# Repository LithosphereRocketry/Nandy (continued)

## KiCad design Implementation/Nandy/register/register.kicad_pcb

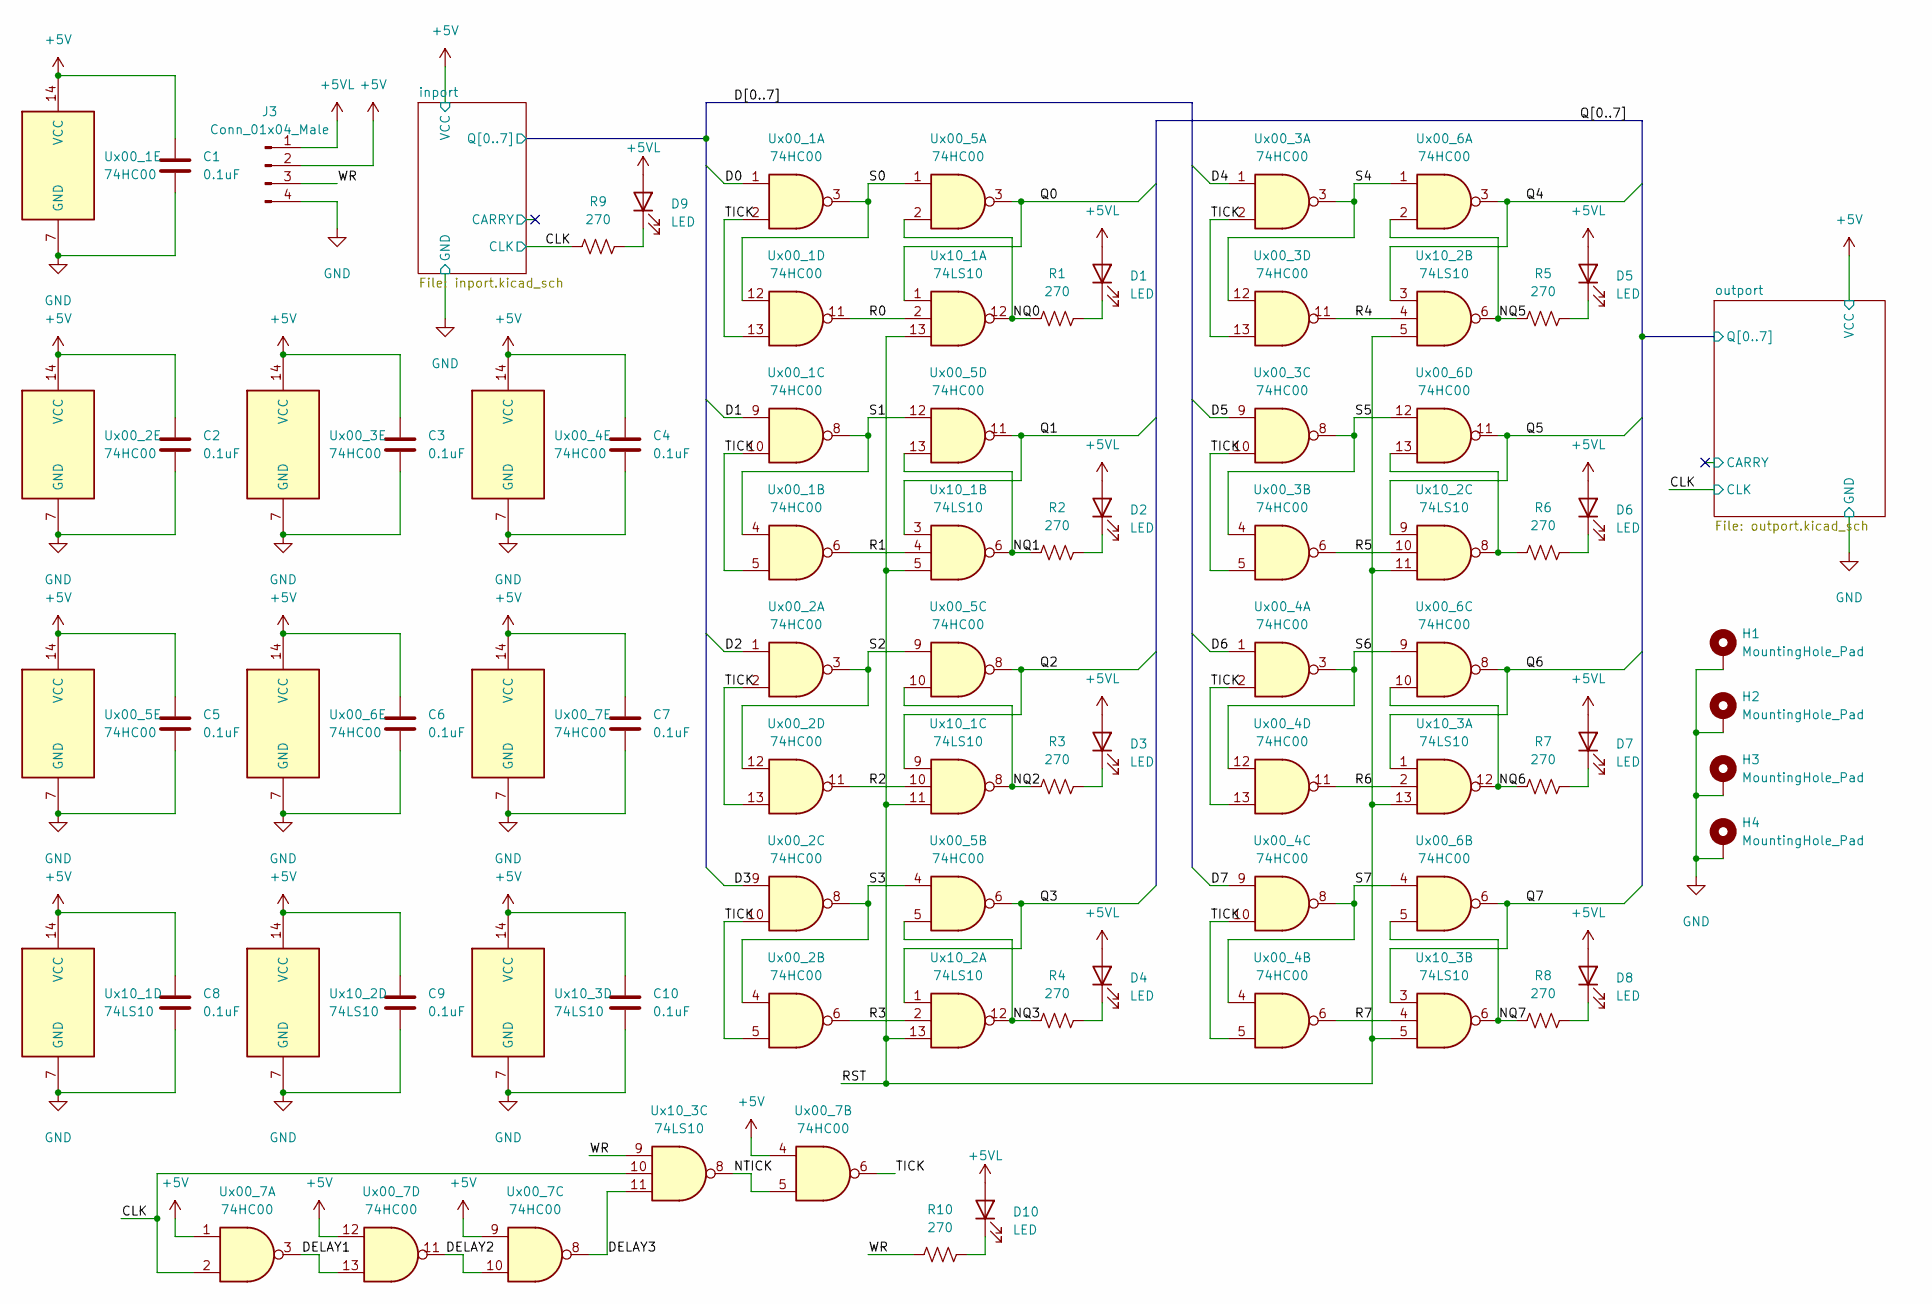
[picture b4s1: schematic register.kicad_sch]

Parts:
C1, C2, C3, C4, C5, C6, C7, C8, C9, C10: 0.1uF; C_Disc_D4.3mm_W1.9mm_P5.00mm
D1, D2, D3, D4, D5, D6, D7, D8, D9, D10: LED; LED_D5.0mm
H1, H2, H3, H4: MountingHole_Pad; MountingHole_3.2mm_M3_Pad_Via
J3: Conn_01x04_Male; SolderWire-0.5sqmm_1x04_P4.6mm_D0.9mm_OD2.1mm
R1, R2, R3, R4, R5, R6, R7, R8, R9, R10: 270; R_Axial_DIN0207_L6.3mm_D2.5mm_P7.62mm_Horizontal
Ux00_1, Ux00_2, Ux00_3, Ux00_4, Ux00_5, Ux00_6, Ux00_7: 74HC00; DIP-14_W7.62mm_Socket
Ux10_1, Ux10_2, Ux10_3: 74LS10; DIP-14_W7.62mm_Socket

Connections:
+5V: C1.1, C2.1, C3.1, C4.1, C5.1, C6.1, C7.1, C8.1, C9.1, C10.1, J3.2, Ux00_1.14 (VCC), Ux00_2.14 (VCC), Ux00_3.14 (VCC), Ux00_4.14 (VCC), Ux00_5.14 (VCC), Ux00_6.14 (VCC), Ux00_7.1, Ux00_7.4, Ux00_7.9, Ux00_7.12, Ux00_7.14 (VCC), Ux10_1.14 (VCC), Ux10_2.14 (VCC), Ux10_3.14 (VCC); also elsewhere on the board
+5VL: D1.2 (A), D2.2 (A), D3.2 (A), D4.2 (A), D5.2 (A), D6.2 (A), D7.2 (A), D8.2 (A), D9.2 (A), D10.2 (A), J3.1
/CLK: R9.1, Ux00_7.2, Ux10_3.10; also elsewhere on the board
/D0: Ux00_1.1; also elsewhere on the board
/D1: Ux00_1.9; also elsewhere on the board
/D2: Ux00_2.1; also elsewhere on the board
/D3: Ux00_2.9; also elsewhere on the board
/D4: Ux00_3.1; also elsewhere on the board
/D5: Ux00_3.9; also elsewhere on the board
/D6: Ux00_4.1; also elsewhere on the board
/D7: Ux00_4.9; also elsewhere on the board
/DELAY1: Ux00_7.3, Ux00_7.13
/DELAY2: Ux00_7.10, Ux00_7.11
/DELAY3: Ux00_7.8, Ux10_3.11
/NQ0: R1.1, Ux00_5.2, Ux10_1.12
/NQ1: R2.1, Ux00_5.13, Ux10_1.6
/NQ2: R3.1, Ux00_5.10, Ux10_1.8
/NQ3: R4.1, Ux00_5.5, Ux10_2.12
/NQ5: R5.1, Ux00_6.2, Ux10_2.6
/NQ6: R7.1, Ux00_6.10, Ux10_3.12
/NQ7: R8.1, Ux00_6.5, Ux10_3.6
/NTICK: Ux00_7.5, Ux10_3.8
/Q0: Ux00_5.3, Ux10_1.1; also elsewhere on the board
/Q1: Ux00_5.11, Ux10_1.3; also elsewhere on the board
/Q2: Ux00_5.8, Ux10_1.9; also elsewhere on the board
/Q3: Ux00_5.6, Ux10_2.1; also elsewhere on the board
/Q4: Ux00_6.3, Ux10_2.3; also elsewhere on the board
/Q5: Ux00_6.11, Ux10_2.9; also elsewhere on the board
/Q6: Ux00_6.8, Ux10_3.1; also elsewhere on the board
/Q7: Ux00_6.6, Ux10_3.3; also elsewhere on the board
/R0: Ux00_1.11, Ux10_1.2
/R1: Ux00_1.6, Ux10_1.4
/R2: Ux00_2.11, Ux10_1.10
/R3: Ux00_2.6, Ux10_2.2
/R4: Ux00_3.11, Ux10_2.4
/R5: Ux00_3.6, Ux10_2.10
/R6: Ux00_4.11, Ux10_3.2
/R7: Ux00_4.6, Ux10_3.4
/RST: Ux10_1.5, Ux10_1.11, Ux10_1.13, Ux10_2.5, Ux10_2.11, Ux10_2.13, Ux10_3.5, Ux10_3.13
/S0: Ux00_1.3, Ux00_1.12, Ux00_5.1
/S1: Ux00_1.4, Ux00_1.8, Ux00_5.12
/S2: Ux00_2.3, Ux00_2.12, Ux00_5.9
/S3: Ux00_2.4, Ux00_2.8, Ux00_5.4
/S4: Ux00_3.3, Ux00_3.12, Ux00_6.1
/S5: Ux00_3.4, Ux00_3.8, Ux00_6.12
/S6: Ux00_4.3, Ux00_4.12, Ux00_6.9
/S7: Ux00_4.4, Ux00_4.8, Ux00_6.4
/TICK: Ux00_1.2, Ux00_1.5, Ux00_1.10, Ux00_1.13, Ux00_2.2, Ux00_2.5, Ux00_2.10, Ux00_2.13, Ux00_3.2, Ux00_3.5, Ux00_3.10, Ux00_3.13, Ux00_4.2, Ux00_4.5, Ux00_4.10, Ux00_4.13, Ux00_7.6
/WR: J3.3, R10.1, Ux10_3.9
GND: C1.2, C2.2, C3.2, C4.2, C5.2, C6.2, C7.2, C8.2, C9.2, C10.2, H1.1, H2.1, H3.1, H4.1, J3.4, Ux00_1.7 (GND), Ux00_2.7 (GND), Ux00_3.7 (GND), Ux00_4.7 (GND), Ux00_5.7 (GND), Ux00_6.7 (GND), Ux00_7.7 (GND), Ux10_1.7 (GND), Ux10_2.7 (GND), Ux10_3.7 (GND); also elsewhere on the board
unnamed: D1.1 (K), R1.2
unnamed: D2.1 (K), R2.2
unnamed: D3.1 (K), R3.2
unnamed: D4.1 (K), R4.2
unnamed: D5.1 (K), R5.2
unnamed: D6.1 (K), R6.2
unnamed: D7.1 (K), R7.2
unnamed: D8.1 (K), R8.2
unnamed: D9.1 (K), R9.2
unnamed: D10.1 (K), R10.2
unnamed: R6.1, Ux00_6.13, Ux10_2.8

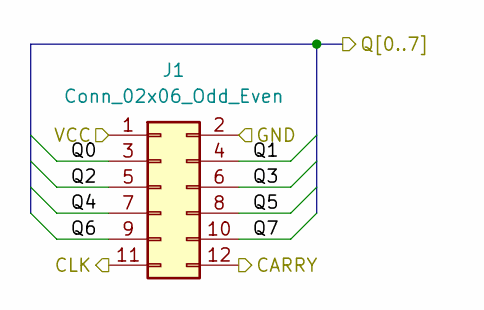
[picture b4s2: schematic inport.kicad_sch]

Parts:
J1: Conn_02x06_Odd_Even; IDC-Header_2x06_P2.54mm_Vertical

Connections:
+5V: J1.1; also elsewhere on the board
/CLK: J1.11; also elsewhere on the board
/D0: J1.3; also elsewhere on the board
/D1: J1.4; also elsewhere on the board
/D2: J1.5; also elsewhere on the board
/D3: J1.6; also elsewhere on the board
/D4: J1.7; also elsewhere on the board
/D5: J1.8; also elsewhere on the board
/D6: J1.9; also elsewhere on the board
/D7: J1.10; also elsewhere on the board
/inport/CARRY: J1.12
GND: J1.2; also elsewhere on the board

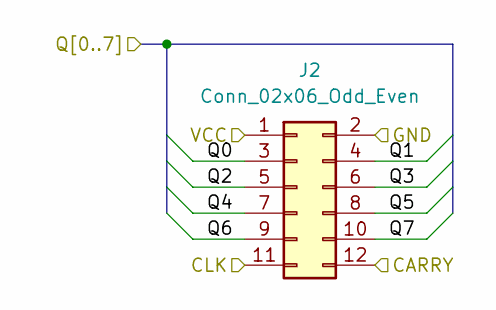
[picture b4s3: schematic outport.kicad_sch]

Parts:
J2: Conn_02x06_Odd_Even; IDC-Header_2x06_P2.54mm_Vertical

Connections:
+5V: J2.1; also elsewhere on the board
/CLK: J2.11; also elsewhere on the board
/Q0: J2.3; also elsewhere on the board
/Q1: J2.4; also elsewhere on the board
/Q2: J2.5; also elsewhere on the board
/Q3: J2.6; also elsewhere on the board
/Q4: J2.7; also elsewhere on the board
/Q5: J2.8; also elsewhere on the board
/Q6: J2.9; also elsewhere on the board
/Q7: J2.10; also elsewhere on the board
/outport/CARRY: J2.12
GND: J2.2; also elsewhere on the board

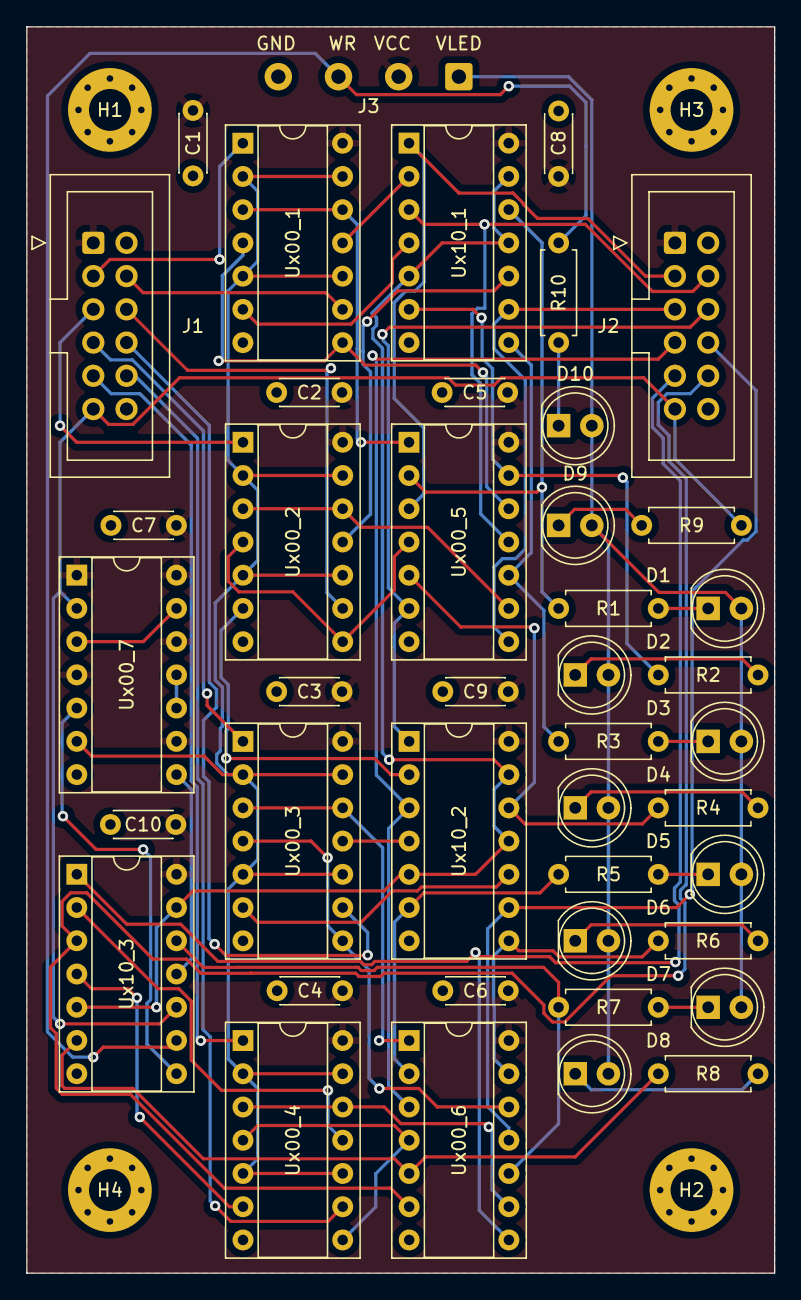
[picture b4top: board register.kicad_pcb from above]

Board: 2 copper layers, 57.1 x 95.2 mm, 47 parts (0 on the bottom side), 61 nets.

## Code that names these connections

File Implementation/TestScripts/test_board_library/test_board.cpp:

#include "test_board.h"

namespace tb {

LiquidCrystal lcd(pins::lcd_rs, pins::lcd_e,
                  pins::lcd_d[4],
                  pins::lcd_d[5],
                  pins::lcd_d[6],
                  pins::lcd_d[7]);

void init() {
    pinMode(pins::lcd_bl, OUTPUT);
    digitalWrite(pins::lcd_bl, HIGH);
    lcd.begin(16, 2);

    pinMode(pins::gnd_det, INPUT);
}

} // namespace tb

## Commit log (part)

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2023-07-29 Some silly experiments in racket
2023-07-29 Basic Racket parsing
2023-07-30 Basic parsing test with fibonacci
2023-07-30 Expression flattening
2023-07-31 Added label resolution
2023-07-31 Added some comments; made move instructions that didnt do anything get deleted
2023-08-05 File reading in emulator + a few quality of life fixes
2023-08-05 Some slight tweaks to fibonacci example
2023-08-05 Added call instructions to emulator; fixed some off-by-one errors
2023-08-07 Set up framework for Icarus Verilog
2023-08-07 Nonfunctional assertions
2023-08-09 Add arithmetic to ProgrammersGuide
2023-08-09 Fixed a typo
2023-08-09 Add description of assembler symbols
2023-08-09 Some basic assertions
2023-08-09 fixed another test; still dont really like it
2023-08-10 Start of top down verilog sim
2023-08-10 Some stack stuff in ProgrammersGuide
2023-08-20 Added support for @static
2023-08-20 Added @static to programmers guide
2023-08-22 Multiplication example; added shifts
2023-09-16 Updated some todos
2023-09-16 D latch (untested)
2023-10-23 Add `goto` macro to assembler
2023-10-29 Further function calling conventions
2023-10-29 Added interrupts to datapath drawing
2023-11-02 Switching to Logisim for high-level design
2023-11-02 Switched jumps to only conditional
2023-11-17 Updated fibonacci for new ISA
2023-11-17 Started fleshing out less common asm instructions
2023-11-18 Added some test circuits to logisim
2023-11-18 Updated assembler to new ISA- needs testing
2023-11-18 Fixed some errors in the instruction definitions
2023-11-18 Updated brk instruction in fib
2023-11-18 Deleted some old tests and updated others
2023-11-18 Fixed some things in asm
2023-11-18 Deleted woefully outdated todo.md
2023-11-18 Test of some layout things
2023-11-18 Made programmers guide 80 columns
2023-11-18 Updated logisim ALU; inverted zero/nzero opcodes
2023-11-18 Fixed emulator to account for new zero op
2023-11-18 Fired a slight programmers guide error
2023-11-19 Added jri and @loc to assembler
2023-11-19 Updated interrupts in circuit
2023-11-19 Added bit conversion utility for Logisim
2023-11-19 Updated .gitignore for binconvert
2023-11-19 Fixed interrupt handling in logisim model
2023-11-19 Fixed a few errors, wrote I/O section
2023-11-19 Removed extraneous gitignore lines
2023-11-19 Combinational logic testing tools
2023-11-19 Updated nand10 testbench
2023-11-21 Redoing test benches and evaulating parts
2023-11-21 Improved handling of tests in makefile
2023-11-21 Test benches for evaluated elements
2023-11-21 Mux verified
2023-11-21 Fixed typo in xornand
2023-11-21 Carry-only adder to calculate 16-bit latency
2023-11-21 Tossed some outdated components in the trash
2023-11-21 Testing for ROM
2023-11-23 Random fuzz test benches
2023-11-23 Finished rest of ALU
2023-11-23 Moved away obsolete assembler files
2023-11-23 Fixed makefile
2023-11-23 Fixed makefile pt2
2023-11-23 Start of instruction reference
2023-11-23 Rest of add/sub ops
2023-11-23 Finished instruction ref
2023-11-27 Basic interrupt handling without logic
2023-11-27 Added basic interrupt support to emulator
2023-11-27 Apparently using goto in a busywait causes the console to pick up extra characters- why????
2023-11-27 Emulator fixed a little but still weird
2023-11-27 Turns out the interrupt issue was actually just bad code
2023-11-28 Updated logisim with jcz
2023-11-30 Put a bunch of old headers in obsolete
2023-12-06 Simulation and guide for manual IR
2023-12-06 Added signum instruction
2023-12-06 Minor typo
2023-12-18 Register design; struggling with kicad automation
2023-12-18 DRC verification working automatically
2023-12-26 Oops big commit; added waveform outputs, RAM simulation, and a few other parts
2023-12-26 Fixed typo
2023-12-26 Logisim sketch of ram bus control
2023-12-26 Some trivial gate primitives
2023-12-26 Start of the control nightmare
2023-12-28 Added waveforms to debug
2023-12-28 Fixed tb error checking
2023-12-28 Gitignored error logs
2023-12-28 M control
2023-12-28 Removed dumpfile from debug because it didnt actually work
2023-12-28 J control
2023-12-28 read and write
2023-12-28 I HAVE SLAIN THE BEAST WRITEACCUMULATOR IS DEAD
2023-12-28 Signal decoder
2023-12-28 Control block latency ~80ns
2023-12-29 Inverted edgegate signal bc it saves one gate in memory
2023-12-29 Some memory stuff, partially tested
2023-12-29 Cleaned up some stuff in circ
2023-12-29 Added negative outputs to latches + added SR latch
2023-12-30 Experimental interrupt control; inverted a signal in control to save a gate again
2023-12-30 Started on the terror that is regfile, inverted another few signals for efficiency
2023-12-30 dy in regfile
2023-12-30 io in regfile
2023-12-31 Saved a mux in register file at the cost of making it even more complicated
2023-12-31 Changes too numerous to list; but VERILOG WORKS
2023-12-31 Switched some random logic to more descriptive layout
2024-01-21 Start of 9-bit mux;
2024-01-21 Working on design principles document
2024-02-03 Working on moving assembler to C
2024-02-03 Scuffed unsustainable + implementation; test of byte-misaligned instructions
2024-02-05 Removed previnst because it sucked
2024-02-22 Some minor signature corrections
2024-02-22 datastructures for new assembler
2024-02-23 Progress on poweroftwo, still sometimes crashes
2024-02-23 Fixed some issues in emulator wrt carry behavior
2024-02-23 power-of-two test works :)
2024-03-05 Very WIP
2024-03-05 Nothing much yet, but created the file for mandel8
2024-03-15 Partial modules schematic
2024-03-15 Removed outdated drawing
2024-03-19 RDA macro in assembler
2024-03-19 Basics of label recognition in the C assembler
2024-03-20 Parsing of nop instructions
2024-03-21 Checking for multiple stacked assembly instructions
2024-03-22 rd without arguments
2024-03-23 Implementation of rd parsing, start of _addi
2024-03-28 Skeleton for parsing code
2024-03-28 Got rid of pointless whole CPU in assembler struct
2024-03-30 Bare minimum shunting yard implementation, argument resolution in assembler
2024-03-30 All the C operations are here now
2024-04-01 Fixed some compiler warnings
2024-04-02 Variables in shuntingyard
2024-04-02 Expression parsing for addi
2024-04-02 Minor tweak to parity, disasm for _addi
2024-04-04 Reorganized instruction def files, added more absolute jumps
2024-04-04 Signal instructions (mostly) implemented
2024-04-05 Reworked instruction defs to be less repetitive
2024-04-11 Apparently sign extension was broken this whole time?
2024-04-11 Fixed sign-ext in the old emu
2024-04-12 Echo command for assembler
2024-04-12 Non-carry shifts
2024-04-13 Add with carry and comparison
2024-04-13 Actually added comparisons
2024-04-13 Assembly assertions
2024-04-13 Bitwise immediate instructions
2024-04-15 Add and subtract operations
2024-04-16 Restructuring to prepare for user macros
2024-04-16 Added capability for hierarchical symbol tables
2024-04-16 Chipping away, not close to done yet
2024-04-17 Allowed labels to be opportunistically resolved on first pass
2024-04-19 ISR label and @loc instructions
2024-04-21 Comparison tools for assembler output
2024-04-21 Patched some (non-critical) memory leaks
2024-04-22 Static memory tools in C asm, slight tweak to racket asm
2024-04-23 Added name display to @echo
2024-04-23 More operations to parser, some notes on future instructions
2024-04-23 Documentation for new assembler
2024-04-23 Move macro, now with less bugs
2024-04-23 More documentation
2024-04-23 Officially deprecated Racket assembler
2024-04-23 Removed old comparison stuff between assemblers
2024-04-25 Reference implementation for malloc
2024-04-26 Start of LCD routines
2024-04-26 Load the file
2024-04-27 Whitespace collapse
2024-04-27 Require ending newlines
2024-04-28 Start of new emulator design
2024-04-28 Cycle counting on new emulator
2024-04-28 Progress on debugger
2024-04-29 Example FAT16 image
2024-04-29 Start refactoring preprocessor
2024-04-29 Improved disassembly scanning
2024-04-30 IO, peek, and poke in debug interface
2024-04-30 Ctrl+C to exit to debugger in emulator
2024-04-30 Makefile for building asm
2024-04-30 Move out newlines
2024-04-30 Character constants
2024-05-01 Fixed mul8
2024-05-03 Fixed right shift & input handling (requires POSIX)
2024-05-03 Fixed stdin avail by just adding requirements
2024-05-04 Made new emulator official
2024-05-04 Reading MBR data
2024-05-06 More functions for LCD
2024-05-06 Removed accidental binary
2024-05-07 Drafting 5.0 standard
2024-05-10 Optimization of gate count :)
2024-05-11 Arithmetic instructions throughout toolchain
2024-05-12 Updated toolchain and Logisim with new ISA, somewhat
2024-05-12 Circ and documentation, wip
2024-05-12 Updated instruction reference
2024-05-12 Removed accidental output file
2024-05-12 Fixed a bug in puthex, more mandelbench
2024-05-13 Chip select in toolchain/docs
2024-05-13 Basic FAT info
2024-05-15 Starting work on reworking register
2024-05-15 Reconciled different Mandelbrot programs
2024-05-16 Start of struct definitions etc
2024-05-18 Progress-ish
2024-05-21 Test fixture kicad file
2024-05-21 Potential I/O expander?
2024-05-23 Connector footprints start
2024-05-24 Progress on designing card layout
2024-05-25 Progress on converting verilog to 5.0
2024-05-27 Removed most of the inc stuff
2024-05-27 Updates to documentation and logisim
2024-05-27 ALU changes working
2024-05-27 Restored old version of .circ file
2024-05-27 Some labels in circ
2024-05-27 Fixed inverted IRX/Y write logic
2024-05-31 Fixed issues with the Verilog interrupt implementation
2024-06-05 Basic Lisp AST parsing
2024-06-05 Symbols in parsing
2024-06-05 Quotes, but they kinda suck
2024-09-17 Most of mux routing
2024-09-17 Simplified datapath drawing
2024-09-28 Datapath updates to remove isp
2024-09-29 progress on new IO setup
2024-10-10 First working setup of new IO layout
2024-10-12 Routed 16C550 serial card
2024-11-01 Check when sp is written
2024-11-07 Control graph datastructure
2024-11-07 Debug print
2024-11-07 Fix j ctrl flow
2024-11-07 Brk is kind of a branch
2024-11-08 In-progress graph traversal
2024-11-08 Analyze interrupt enable
2024-11-08 Recursive block traversal
2024-11-08 Bugfixes
2024-11-12 Added extra scary warning if a block is reachable with multiple interrupt modes
2024-11-12 Split value and conflict flags into separate values to make more complex analysis smoother
2024-11-15 Static analysis of absolute jumps
2024-12-24 Simple text fixturing tools
2025-02-14 Some more work on module boards
2025-11-22 A bunch of assorted WIP on IO rework
2025-11-23 Basic slow memcpy routine, and fixed a bug in ioa
2025-11-29 Separate interrupt stack in emu, some better documentation, some more work on IO
2025-11-29 Remove a bunch of not-ready-for-prod eeprom stuff
2025-12-20 Reworked at least to the point of compiling
2025-12-20 Fixed interrupt handling and add PC-relative and conditional call instructions
2025-12-20 Re-add NOP instruction
2025-12-21 Updated several things to 7.0 design
2025-12-21 WIP CF test, some work on CF support in emulation, more reasonable assembler output text
2025-12-21 marginal progress on CF
2025-12-25 Fixed a few assembler bugs and improved ergonomics for assembler and emulator
2026-01-17 Basic serial implementation, and rework how IO pseudo-register is handled in emulation to make a lot of stuff easier
2026-01-17 fix some typos and left-in debug
2026-01-18 Fixed a bug in cset, and memcpy example
2026-01-19 Merged stash changes to compactflash emulation
2026-01-20 Help text in CLI options, and a few cleanup things
2026-01-20 Basic support for card detection
2026-01-20 Card detection and removed an unused parameter
2026-05-24 Fix a type mismatch in interrupt handler
2026-05-25 Convert postincrement to preincrement to save a few gates
2026-05-25 Fixed nop, oops
2026-05-25 ALU portion of datapath
2026-05-26 Datapath done(tm), working on control
2026-05-28 In theory, all control signals done
2026-05-28 Datapath painting done wooooo
2026-05-28 Cherry pick type fix that was lost for some reason
2026-05-28 First handful of instructions working correctly!
2026-05-28 Print string program running in Verilog
2026-05-29 Update documentation for 7.0 architecture
2026-05-30 Basic sector reads working, and very basic cf emulation
2026-06-28 Fix a very dumb card emu bug
2026-06-28 Baby steps toward fpga
2026-06-28 Basic toplevel working on fpga
2026-06-29 Text output working on fpga
